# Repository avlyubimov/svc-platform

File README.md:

# SVC Platform — Smart Vehicle Controller

<p align="center">
  Open modular hardware, firmware, and mobile software for controlling
  auxiliary equipment on motorcycles and other vehicles.
</p>

**Reference Vehicle #001:** BMW R1200GS K25 2007<br>
**VIN:** WB10307A97ZU65028

## Mission

SVC should allow new functionality to be added primarily through configuration,
plugins, firmware updates, or Logic Board replacement without redesigning the
Power Board.

## Current status

Architecture v1.0 is frozen. Firmware safety, configuration, role mapping,
rule execution, CAN safety, update policy, and PWM ownership have host-tested
scaffolds.

The three boards are moving through the controlled EVT lifecycle independently:

| Board | Current repository state | Release boundary |
| --- | --- | --- |
| **PB-100** | `EVT-LAYOUT-AUTHORIZED` | Partial layout only; fabrication and production remain blocked |
| **LB-100** | `EVT-FAB-AUTHORIZED` | One segregated five-piece bare-PCB EVT package only |
| **FB-100** | `EVT-LAYOUT-AUTHORIZED` | Layout may continue; fabrication and production remain blocked |

These states describe the current `master` baseline. They do not authorize a
combined board order or production release. Detailed and machine-checked gates
are tracked in
[`docs/product/final-readiness.md`](docs/product/final-readiness.md).

## Mobile application

<p align="center">
  
  &nbsp;&nbsp;&nbsp;&nbsp;
  
</p>

SVC Mobile is being developed for iOS and Android. It provides the foundation
for live telemetry, diagnostics, vehicle data, channel control, event history,
configuration, and phone-mediated firmware updates. CHIGEE AIO-6 is treated as
a CarPlay/Android Auto projection host; the applications run on the phone.

The committed mobile baseline includes SwiftUI and Jetpack Compose
applications, BLE and protocol layers, mock data, projection scaffolds, a
GitHub Releases client, and signed-update validation. Physical channel control,
live BLE integration, and firmware transfer/installation remain disabled or
mock-backed until hardware validation closes the applicable safety gates.

The images above use only the project-owned SVC identity.
Vehicle-manufacturer artwork is not part of this repository presentation.

### SVC Ride Dashboard

Dashboard v1 is implemented for the SwiftUI and Jetpack Compose phone targets.
It uses separate versioned vehicle-performance profiles, explicit telemetry
quality states, profile-driven tachometer zones, SVC-estimated lean, Day/Night
themes, Reduce Motion, and adaptive landscape/portrait layouts. Missing CAN
signals remain `—`; gear is not inferred from speed and RPM. CarPlay and
Android Auto retain a separate, reduced information-only template.

- [Mobile overview and local build commands](software/mobile/README.md)
- [iOS application](software/mobile/ios/SVCMobile/README.md)
- [Android application](software/mobile/android/README.md)
- [Firmware update trust boundary](docs/architecture/firmware-update.md)
- [SVC identity assets](software/mobile/branding/svc/README.md)
- [Ride Dashboard implementation boundary](software/mobile/docs/ride-dashboard-roadmap.md)

## Validation

```bash
make check
```

This runs repository readiness checks, KiCad validation, firmware configuration
validation and host tests, mobile protocol tests, and release-policy checks.
The same command runs in GitHub Actions on push and pull request.

Platform-specific mobile workflows additionally build and test the Android and
iOS projects in GitHub Actions.

## Repository structure

```text
docs/                 Architecture, ADR, requirements, production docs
hardware/             KiCad and mechanical files
firmware/             Embedded firmware, bootloader, plugins
software/             SVC Studio and SVC Mobile
can-db/               Vehicle CAN databases
production/           BOM, Gerber, Pick&Place, assembly docs
tools/                Readiness, protocol, security, and release validation
```

## Board naming

- **PB-100** — Power Board, intended to remain stable for 10–15 years.
- **LB-100** — Logic Board, replaceable and upgradeable.
- **FB-100** — Front Panel Board, service interface and indicators.

## Hard rule

**Power Board is sacred.**

New features should not require Power Board redesign unless all configuration,
plugin, firmware, and Logic Board options are exhausted.

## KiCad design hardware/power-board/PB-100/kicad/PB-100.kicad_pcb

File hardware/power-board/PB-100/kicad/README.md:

# PB-100 KiCad Project

Status: `EVT-LAYOUT-AUTHORIZED`; connectivity-complete layout; fabrication blocked

This directory contains the controlled Rev.1 EVT KiCad project for PB-100.

## Current boundary

- `PB-100.kicad_pro`: project metadata scaffold.
- `PB-100.kicad_sch`: value-bearing top-level schematic with linked child
  sheets.
- `sheets/*.kicad_sch`: child sheets with role-agnostic `OUT1`..`OUT10` nets
  and the reviewed CAN1 DNP/open safety path.
- `sym-lib-table`: project-local symbol library table.
- `fp-lib-table`: project-local footprint library table.
- `lib/PB100.kicad_sym` and `lib/PB100Gen.kicad_sym`: controlled project-local
  symbols.
- `lib/PB100.pretty/`: controlled project-local footprints.
- `PB-100-routing.csv`: complete deterministic routing manifest.

The controlled `PB-100.kicad_pcb` places all 414 footprint-bound schematic
parts plus eight mechanical holes on the reviewed 150 mm x 90 mm, eight-layer
outline. It contains 5,677 segments, 910 conventional through vias, 39
adjacent-layer microvias and 38 zones. KiCad 10.0.4 refill reports zero
unconnected items; schematic parity contains only the eight intentional
board-only mounting holes.

The 39 `0.30/0.10 mm` microvias are explicit HDI manufacturing constraints.
They include stacked F.Cu-to-In3.Cu and B.Cu-to-In5.Cu transitions. U3 pads 2
and 9 also contain filled/capped conventional through via-in-pad features.
Supplier sequential-lamination, aspect-ratio, registration, filling/capping,
inspection, yield and quote acceptance remain mandatory.

ADR-0019 and ADR-0020 permit controlled board import, placement, routing,
copper pours and extraction while the final EVT schematic review remains open.
There are no manufacturing outputs; Gerber, drill, pick-and-place, BOM/CPL and
zipped manufacturing outputs remain blocked until
`EVT-FAB-AUTHORIZED` after DRC, parity, 40 A electrothermal/clamp-loop review,
DFM, connector fit and laboratory safety review.

## Source documents

- `../PB-100-schematic-capture-plan.md`
- `../PB-100-schematic-capture-work-queue.csv`
- `../PB-100-review-release-manifest.csv`
- `../PB-100-schematic-readiness-dashboard.csv`
- `../PB-100-net-naming.md`
- `../PB-100-schematic-instance-plan.csv`
- `../PB-100-schematic-instance-symbol-map.csv`
- `../PB-100-schematic-sheet-reference-map.csv`
- `../PB-100-schematic-net-domain-plan.csv`
- `../PB-100-output-channel-pin-contract.csv`
- `../PB-100-output-controller-pin-template.csv`
- `../PB-100-output-net-expansion.csv`
- `../PB-100-output-stage-design-values.csv`
- `../PB-100-input-controller-pin-template.csv`
- `../PB-100-input-protection-pin-contract.csv`
- `../PB-100-input-power-design-values.csv`
- `../PB-100-current-monitor-pin-template.csv`
- `../PB-100-logic-buck-pin-template.csv`
- `../PB-100-logic-power-design-placeholders.csv`
- `../PB-100-logic-power-design-values.csv`
- `../PB-100-kicad-prep.md`
- `../PB-100-kicad-sheet-manifest.csv`
- `../PB-100-kicad-footprint-plan.csv`
- `../PB-100-footprint-binding-inventory.csv`
- `../PB-100-symbol-mpn-readiness.csv`
- `../PB-100-symbol-capture-worklist.csv`
- `../PB-100-symbol-pin-evidence.csv`
- `../PB-100-symbol-open-items.md`
- `../PB-100-schematic-freeze-checklist.md`
- `../PB-100-pcb-layout-start-checklist.csv`
- `../PB-100-mechanical-envelope-inventory.csv`
- `../PB-100-schematic-freeze-gap-register.csv`
- `../PB-100-validation-traceability.csv`
- `../PB-100-test-point-plan.csv`
- `../PB-100-fault-response-matrix.csv`
- `../PB-100-can1-safety-verification.csv`
- `../../../../production/bom/pb100_assembly_sourcing_recheck.csv`
- `../../../../production/bom/pb100_sourcing_evidence_snapshot.csv`
- `../../../../production/board-order/three_board_footprint_binding_status.csv`
- `../../../../production/board-order/three_board_mechanical_envelope_status.csv`
- `../../../../firmware/configs/hardware/pb-100-capabilities.json`

## Next controlled work

1. Review `../PB-100-evt-fab-review-checklist.csv`, ADR-0020 and
   `../PB-100-layout-progress.md`.
2. Open `PB-100.kicad_pro` in KiCad.
3. Perform the 40 A electrothermal, switch/clamp-loop, Kelvin, rail, CAN1,
   connector and safety review against the tracked layout.
4. Obtain supplier HDI stack/DFM acceptance and filled/capped via-in-pad
   confirmation before any fabrication authorization.
5. Preserve all generic outputs, option footprints and DNP variants during
   review changes.
6. Do not create Gerbers, drills, pick-place, BOM/CPL, manufacturing ZIP files,
   fabrication packages or PCBA orders until `EVT-FAB-AUTHORIZED`.

## Validation

Run from repository root:

```bash
python3 tools/validate_pb100.py
python3 tools/validate_pb100_layout.py
```

The validator intentionally fails if manufacturing artifacts appear before
layout review and order evidence close.

The validator requires `kicad-cli` version `10.0.4`. It fails if KiCad is
missing or a different version is installed.

The validator also rejects `sheet-placeholder`/`Placeholder sheet` markers,
runs schematic ERC, requires zero reported violations, exports a temporary KiCad
S-expression netlist, checks that all child sheets in
`PB-100-kicad-sheet-manifest.csv` are linked from the top-level schematic, and
requires at least 20 schematic components plus 20 electrical nets in the exported
netlist. Empty child sheets are therefore not allowed to pass CI.

The current child sheets use passive preliminary class-symbol pins so ERC checks
hierarchy, net continuity, and capture completeness without treating abstract
planning symbols as final electrical models. Schematic freeze must replace those
abstract instances with reviewed final pin electrical types, values, footprints,
and MPN selections.

KiCad schematic and symbol files are also checked for accessory-role tokens such
as `FOG`, `USB`, `SEAT`, `CHIGEE`, `DVR`, and `BRAKE`. PB-100 output artifacts
must use generic `OUT1`..`OUT10` naming only. The protected manual-request inputs
`FOG_A_SW_IN` and `FOG_B_SW_IN` are the only explicit exceptions; they do not
assign roles to outputs and cannot bypass Output Manager authorization.

Rows in `PB-100-symbol-capture-worklist.csv` that say `preliminary symbol
created` are checked against `lib/PB100.kicad_sym`; those symbols must stay
excluded from BOM and board output until schematic freeze.

`PB-100-symbol-pin-evidence.csv` records the official data-sheet pin tables used
for concrete MPN symbols and the internal schematic-class pin contracts used for
non-final class symbols. Validation checks each recorded pin number/name against
the KiCad symbol library.

`PB100_JPB1_100PIN_PRELIM` is generated from
`PB-100-b2b-pin-map.csv`; validation checks all 100 connector pin names and
numbers directly against that map.

The readiness dashboard and pin/value contract CSVs are checked against the
instance map, JPB1 pin map, net-domain plan, and freeze policy. Layout-start
work is now controlled by `../PB-100-pcb-layout-start-checklist.csv`.

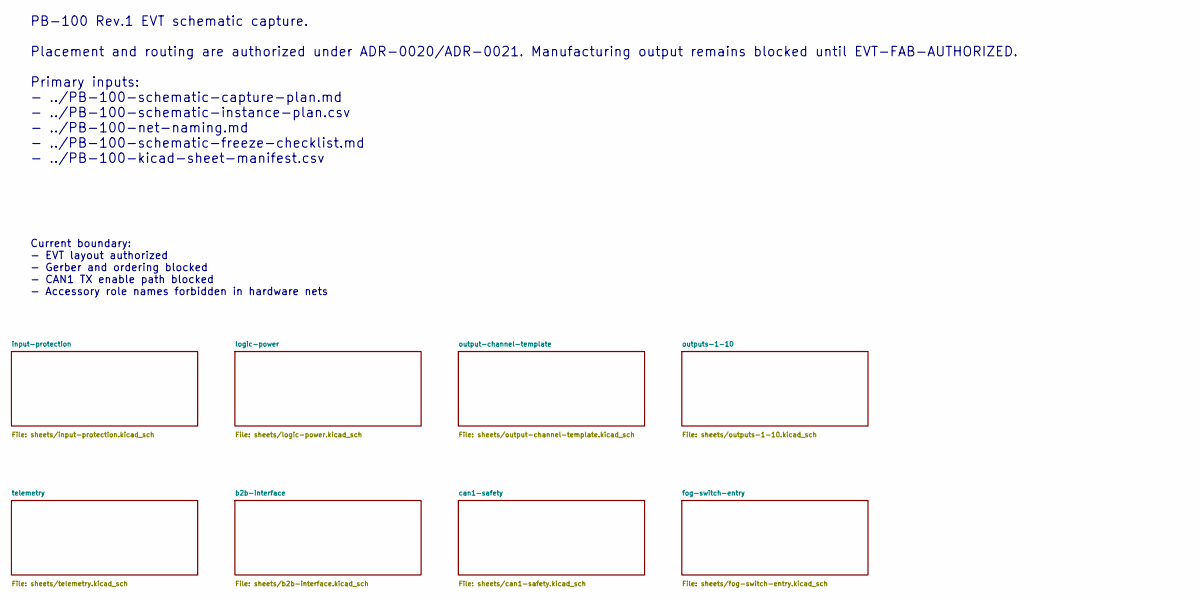
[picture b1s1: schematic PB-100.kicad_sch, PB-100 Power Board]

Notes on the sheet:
PB-100 Rev.1 EVT schematic capture. Placement and routing are authorized under ADR-0020/ADR-0021. Manufacturing output remains blocked until EVT-FAB-AUTHORIZED. Primary inputs: - ../PB-100-schematic-capture-plan.md - ../PB-100-schematic-instance-plan.csv - ../PB-100-net-naming.md - ../PB-100-schema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
Current boundary: - EVT layout authorized - Gerber and ordering blocked - CAN1 TX enable path blocked - Accessory role names forbidden in hardware nets

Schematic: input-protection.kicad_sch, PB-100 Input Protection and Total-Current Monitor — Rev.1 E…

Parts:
C20: 100nF 50V X7R DIFF; C0603
C21: 1nF 100V C0G; C0603
C22: 100nF 16V X7R; C0603
C23: 1nF PB I2C INT FILTER DNP; C0603; not fitted
C24: 10nF 50V X7R; C0603
CCAP1: 100nF 25V X7R; C0603
CSN1: 1nF 100V C0G DNP; C0603; not fitted
CSN2: 1nF 200V C0G DNP; C0603; not fitted
CVS1: CGA6N3X7R2A225M230AE 2.2uF 100V X7R; Ceff>=1uF@56V; C1210
D1: SM8S33AHM3/I; DO-218AC_Vishay_SM8S; not fitted
DZVS1: 56V AUTOMOTIVE ZENER; SOD-123F
J1: INPUT_CONNECTOR_CLASS_PRELIM (OFF-BOARD)
JIN1: 40A PCB PIGTAIL TO NEAR-BATTERY 50A FUSE; POWER_PIGTAIL_2xTH_40A
JISO1: EVT INPUT-STAGE ISOLATION LINK — FITTED FOR NORMA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; EVT_INPUT_ISOLATION_LINK_M4
Q1: IAUT300N08S5N012ATMA2; PG-HSOF-8-1_TOLL_Infineon
Q2: IAUTN15S6N025ATMA1; PG-HSOF-8-1_TOLL_Infineon
R3, R4: 42.2k 1%; R0603
R5: 1.00k 1%; R0603
R6: 10k 1%; R0603
R7: 0R REPLACEABLE Q1 GATE; R0603
R8: 0R REPLACEABLE Q2 GATE; R0603
R20, R21: 10R 0.1% SHUNT FILTER; R0603
R22: 1k 1% VBUS FILTER; R0603
R23: 10k PB I2C SDA PULL DNP; R0603; not fitted
R24: 10k PB I2C SCL PULL DNP; R0603; not fitted
R25: 47k PB I2C INT PULL DNP; R0603; not fitted
R26: 0R INPUT FAULT AGGREGATE; R0603
R27: 200k 0.1% 100V; R0603
R28: 10k 0.1%; R0603
R29: 1k 0.1%; R0603
RSH1: CSS4J-4026R-L500F 0.5mR 5W FOUR-TERMINAL; CSS4J-4026_Bourns
RSN1: 100R DNP Q1 DAMPING; R0603; not fitted
RSN2: 100R DNP Q2 DAMPING; R0603; not fitted
TP001: TEST GND; TestPoint_SMD_1.5mm
TP003: TEST VBAT_RAW; TestPoint_SMD_1.5mm
TP004: TEST VBAT_REV_PROT; TestPoint_SMD_1.5mm
TP005: TEST VBAT_PROT; TestPoint_SMD_1.5mm
TP006: TEST IIN_SHUNT_HI; TestPoint_SMD_1.5mm
TP007: TEST IIN_SHUNT_LO; TestPoint_SMD_1.5mm
TP008: TEST VBAT_SENSE; TestPoint_SMD_1.5mm
TP009: TEST IIN_SENSE; TestPoint_SMD_1.5mm
TP062: TEST Q1_GATE; TestPoint_SMD_1.5mm
TP063: TEST Q2_GATE; TestPoint_SMD_1.5mm
TP064: TEST INPUT_COMMON_SOURCE; TestPoint_SMD_1.5mm
TP065: TEST VBAT_PROT_PRELINK; TestPoint_SMD_1.5mm
U1: LM74930QRGERQ1; VQFN-24_RGE_4x4mm_P0.5mm_EP2.4mm
U2: INA228AQDGSRQ1 TOTAL CURRENT MONITOR; VSSOP-10_L3.0-W3.0-P0.50-LS4.9-BL

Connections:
IIN_MON_N: C20.2, R21.2, U2.9 (IN-)
IIN_MON_P: C20.1, R20.2, U2.10 (IN+)
IIN_SHUNT_HI: R20.1, RSH1.3 (SNS_IN), TP006.1 (IIN_SHUNT_HI)
IIN_SHUNT_LO: R21.1, RSH1.4 (SNS_OUT), TP007.1 (IIN_SHUNT_LO)
IIN_VBUS_FILTERED: C21.1, R22.2, U2.8 (VBUS)
INPUT_COMMON_SOURCE: CSN1.2, CSN2.2, Q1.2 (S), Q1.3 (S), Q1.4 (S), Q1.5 (S), Q1.6 (S), Q1.7 (S), Q1.8 (S), Q2.2 (S), Q2.3 (S), Q2.4 (S), Q2.5 (S), Q2.6 (S), Q2.7 (S), Q2.8 (S), TP064.1 (INPUT_COMMON_SOURCE), U1.2 (A), U1.15 (OUT)
INPUT_PROT_FAULT_N: R26.1, U1.12 (FLT)
LB_3V3_IO: R23.1, R24.1, R25.1; also elsewhere on the board
LM74930_CAP: CCAP1.1, U1.23 (CAP)
LM74930_OV: R4.2, R5.1, U1.5 (OV)
LM74930_OV_TOP_MID: R3.2, R4.1
LM74930_VS: CCAP1.2, CVS1.1, DZVS1.1, R6.2, U1.4 (UVLO), U1.6 (EN), U1.7 (MODE), U1.22 (VS)
PB_5V_OUT: C22.1, U2.6 (VS); also elsewhere on the board
Q1_DGATE: R7.1, U1.1 (DGATE)
Q1_GATE: Q1.1 (G), R7.2, TP062.1 (Q1_GATE)
Q1_SNUB: CSN1.1, RSN1.2
Q2_GATE: Q2.1 (G), R8.2, TP063.1 (Q2_GATE)
Q2_HGATE: R8.1, U1.14 (HGATE)
Q2_SNUB: CSN2.1, RSN2.2
VBAT_PROT: JISO1.2 (BOARD_LOADS), R22.1, R27.1, TP005.1 (VBAT_PROT); also elsewhere on the board
VBAT_PROT_PRELINK: JISO1.1 (INPUT_STAGE), RSH1.2 (PWR_OUT), TP065.1 (VBAT_PROT_PRELINK)
VBAT_RAW: D1.1 (K), J1.1 (VBAT_RAW), JIN1.1 (VBAT_RAW), Q2.Tab (D), R3.1, R6.1, RSN2.1, TP003.1 (VBAT_RAW)
VBAT_REV_PROT: Q1.Tab (D), RSH1.1 (PWR_IN), RSN1.1, TP004.1 (VBAT_REV_PROT), U1.18 (ISCP), U1.19 (CS-), U1.20 (CS+), U1.24 (C)
VBAT_SENSE_RAW: R27.2, R28.1, R29.1

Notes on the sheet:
Work queue: CAP-INP. ADR-0018/0019/0020 implementation. The raw-side 150 V Q2 and protected-side 80 V Q1 retain the reviewed LM74930-Q1 common-source hard-cutoff topology. RSH1 is a 0.5 mOhm four-terminal shunt. JISO1 is the mandatory removable input-stage isolation link; opening it prevents VBAT_P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

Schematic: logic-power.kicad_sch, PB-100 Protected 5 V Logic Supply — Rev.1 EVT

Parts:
C30: 2.2uF 100V X7R; C1210
C31: 100nF 100V X7R; C0805
C32: 10uF 100V BULK CANDIDATE; C1210
C33: 2.2nF 50V X7R; C0603
C34, C35: 22uF 10V X7R; C1210
C36: 100nF 16V X7R; C0603
C37: 10nF PGOOD FILTER DNP; C0603; not fitted
C38: 3.3nF 100V C0G TYPE3 CA; C0603
C39: 180pF 50V C0G TYPE3 CB; C0603
C40: 1nF 100V C0G DNP; C0603; not fitted
L1: 47uH SHIELDED AEC-Q200; Isat>=2.2A Irms>=1.2A; Inductor_12x12mm
R30: 332k 1%; R0603
R31: 100k 1%; R0603
R32: 41.2k 1%; R0603
R33: 158k 0.1%; R0603
R34: 49.9k 0.1%; R0603
R35: 47k PGOOD PULL-UP; R0603
R36: 110k 1% TYPE3 RA; R0603
R37: 100R BUCK SNUBBER DNP; R0603; not fitted
TP010: TEST PB_5V_OUT; TestPoint_SMD_1.5mm
TP011: TEST PB_PWR_GOOD; TestPoint_SMD_1.5mm
U3: LM5164QDDATQ1 100V 1A BUCK; SOIC-8_L4.9-W3.9-P1.27-LS6.0-BL-EP2.9

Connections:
BUCK_BST: C33.1, U3.7 (BST)
BUCK_EN_UVLO: R30.2, R31.1, U3.3 (EN/UVLO)
BUCK_FB: C39.2, R33.2, R34.1, U3.5 (FB)
BUCK_RAMP: C38.2, C39.1, R36.1
BUCK_RON_SET: R32.1, U3.4 (RON)
BUCK_SNUB: C40.1, R37.2
BUCK_SW: C33.2, C38.1, L1.1, R37.1, U3.8 (SW)
LB_3V3_IO: R35.1; also elsewhere on the board
PB_5V_OUT: C34.1, C35.1, C36.1, L1.2, R33.1, R36.2, TP010.1 (PB_5V_OUT); also elsewhere on the board
VBAT_PROT: C30.1, C31.1, C32.1, R30.1, U3.2 (VIN); also elsewhere on the board

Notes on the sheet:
Work queue: CAP-LOGIC. LM5164-Q1 100 V synchronous buck, 5.0 V / 1 A planning limit. The 300 kHz candidate uses 41.2k RON, 47uH shielded inductor, and a type-3 ripple-injection network. Switch-node copper must remain compact; thermal vias under the exposed pad and routed EMI evidence are required a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

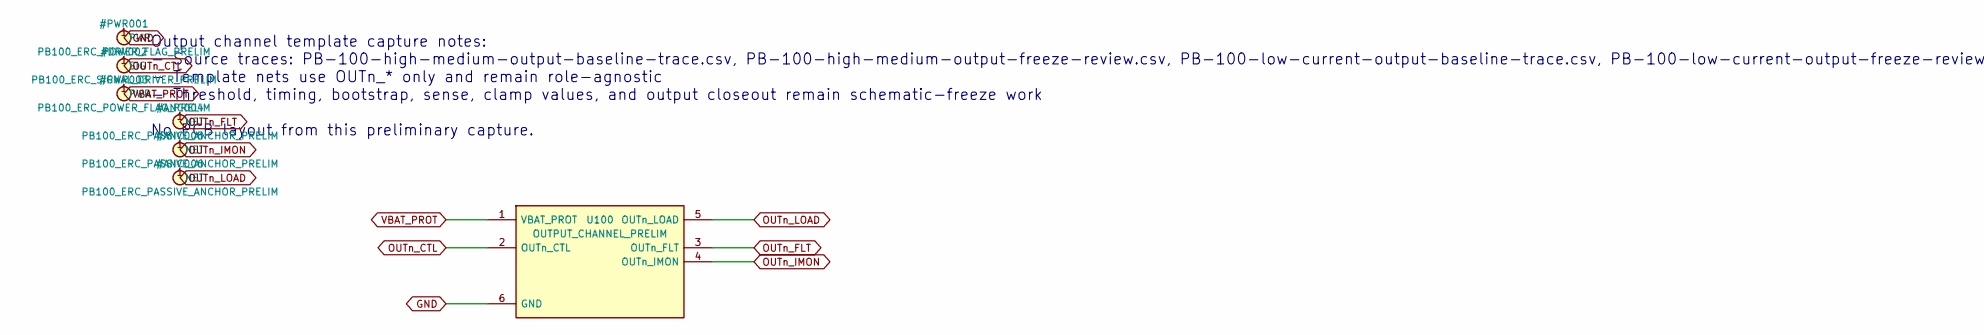
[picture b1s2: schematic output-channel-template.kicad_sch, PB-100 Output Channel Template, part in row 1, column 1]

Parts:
U100: OUTPUT_CHANNEL_PRELIM

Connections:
unnamed: U100.1 (VBAT_PROT), U100.6 (GND)
unnamed: U100.3 (OUTn_FLT), U100.4 (OUTn_IMON), U100.5 (OUTn_LOAD)

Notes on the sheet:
Output channel template capture notes: - Source traces: PB-100-high-medium-output-baseline-trace.csv, PB-100-high-medium-output-freeze-review.csv, PB-100-low-current-output-baseline-trace.csv, PB-100-low-current-output-freeze-review.csv, PB-100-output-stage-value-freeze-checklist.csv, PB-100-output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

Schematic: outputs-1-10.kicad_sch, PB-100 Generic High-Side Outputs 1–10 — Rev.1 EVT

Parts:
C1101, C1201, C1301, C1401, C1501, C1601, C1701, C1801, C1901, C2001: 680nF 16V X7R TMR; C0603
C1102, C1202, C1302, C1402, C1502, C1602, C1702, C1802, C1902, C2002: 470nF 25V X7R BST; C0603
C1103, C1203, C1303, C1403, C1503, C1603, C1703, C1803, C1903, C2003: 1nF 50V C0G ISCP; C0603
C1104, C1204, C1304, C1404, C1504, C1604, C1704, C1804, C1904, C2004: 100nF 100V X7R VS; C0805
C1105, C1205, C1305, C1405, C1505, C1605, C1705, C1805, C1905, C2005: 10nF 50V X7R IMON; C0603
C1106, C1206, C1306, C1406, C1506, C1606, C1706, C1806, C1906, C2006: 1nF 25V DNP GATE-SLEW; C0603; not fitted
C1107, C1207, C1307, C1407, C1507, C1607, C1707, C1807, C1907, C2007: 1nF 100V C0G DNP SNUBBER; C0603; not fitted
DCL101, DCL102, DCL103, DCL104, DCL105, DCL106, DCL107, DCL108, DCL109, DCL110: STPS40170CGY-TR 2x20A 170V COMMON-CATHODE; D2PAK_3_CommonCathode
F101, F102, F103, F104, F105, F106, F107, F108, F109, F110: OUTPUT_FUSE_CLASS_PRELIM (OFF-BOARD)
J101, J102, J103, J104, J105, J106, J107, J108, J109, J110: OUTPUT_CONNECTOR_CLASS_PRELIM (OFF-BOARD)
Q101, Q102, Q103, Q104, Q105, Q106, Q107, Q108, Q109, Q110: IAUT300N08S5N012ATMA2; PG-HSOF-8-1_TOLL_Infineon
QT101, QT102, QT103, QT104, QT105, QT106, QT107, QT108, QT109, QT110: MMBT3904-Q REMOTE TEMP DIODE; SOT-23-3_DBZ_TI
R1101, R1201, R1301, R1401, R1501, R1601, R1701, R1801, R1901, R2001: 470k 1%; R0603
R1102, R1202, R1302, R1402, R1502, R1602, R1702, R1802, R1902, R2002: 103k 1%; R0603
R1103, R1203, R1303, R1403, R1503, R1603, R1703, R1803, R1903, R2003: 12.4k 1%; R0603
R1104, R1204, R1304, R1404, R1504, R1604, R1704, R1804, R1904, R2004: 100R 1% RSET; R0603
R1105, R1305, R1405, R1505, R1605, R1705, R1805, R1905, R2005: 49.9k 1% RIWRN; R0603
R1106: 3.40k 1% RISCP; R0603
R1107, R1207, R1307, R1407, R1507, R1607, R1707, R1807, R1907, R2007: 12.1k 1% RIMON; R0603
R1108, R1208, R1308, R1408, R1508, R1608, R1708, R1808, R1908, R2008: 1k 1% IMON ADC SERIES; R0603
R1109, R1209, R1309, R1409, R1509, R1609, R1709, R1809, R1909, R2009: 100k CTL DEFAULT-OFF; R0603
R1110, R1210, R1310, R1410, R1510, R1610, R1710, R1810, R1910, R2010: 3.3R 1% REPLACEABLE PU; R0603
R1111, R1211, R1311, R1411, R1511, R1611, R1711, R1811, R1911, R2011: 0R REPLACEABLE PD; R0603
R1112, R1212, R1312, R1412, R1512, R1612, R1712, R1812, R1912, R2012: 10k FLT PULL-UP; R0603
R1113, R1213, R1313, R1413, R1513, R1613, R1713, R1813, R1913, R2013: 100R DNP DRAIN-SOURCE SNUBBER; R0603; not fitted
R1205: 67.3k 1% RIWRN; R0603
R1206: 2.61k 1% RISCP; R0603
R1306, R1406, R1606, R1706, R2006: 3.83k 1% RISCP; R0603
R1506, R1806, R1906: 3.74k 1% RISCP; R0603
RSH101: CSS4J-4026 1.0mR FOUR-TERMINAL; CSS4J-4026_Bourns
RSH102: CSS4J-4026 0.5mR FOUR-TERMINAL; CSS4J-4026_Bourns
RSH103, RSH104, RSH106, RSH107, RSH110: CSS4J-4026 1.5mR FOUR-TERMINAL; CSS4J-4026_Bourns
RSH105, RSH108, RSH109: CSS4J-4026 3.0mR FOUR-TERMINAL; CSS4J-4026_Bourns
TP022: TEST OUT1_CTL; TestPoint_SMD_1.5mm
TP023: TEST OUT1_FLT; TestPoint_SMD_1.5mm
TP024: TEST OUT1_IMON; TestPoint_SMD_1.5mm
TP025: TEST OUT1_SWITCHED; TestPoint_SMD_1.5mm
TP026: TEST OUT2_CTL; TestPoint_SMD_1.5mm
TP027: TEST OUT2_FLT; TestPoint_SMD_1.5mm
TP028: TEST OUT2_IMON; TestPoint_SMD_1.5mm
TP029: TEST OUT2_SWITCHED; TestPoint_SMD_1.5mm
TP030: TEST OUT3_CTL; TestPoint_SMD_1.5mm
TP031: TEST OUT3_FLT; TestPoint_SMD_1.5mm
TP032: TEST OUT3_IMON; TestPoint_SMD_1.5mm
TP033: TEST OUT3_SWITCHED; TestPoint_SMD_1.5mm
TP034: TEST OUT4_CTL; TestPoint_SMD_1.5mm
TP035: TEST OUT4_FLT; TestPoint_SMD_1.5mm
TP036: TEST OUT4_IMON; TestPoint_SMD_1.5mm
TP037: TEST OUT4_SWITCHED; TestPoint_SMD_1.5mm
TP038: TEST OUT5_CTL; TestPoint_SMD_1.5mm
TP039: TEST OUT5_FLT; TestPoint_SMD_1.5mm
TP040: TEST OUT5_IMON; TestPoint_SMD_1.5mm
TP041: TEST OUT5_SWITCHED; TestPoint_SMD_1.5mm
TP042: TEST OUT6_CTL; TestPoint_SMD_1.5mm
TP043: TEST OUT6_FLT; TestPoint_SMD_1.5mm
TP044: TEST OUT6_IMON; TestPoint_SMD_1.5mm
TP045: TEST OUT6_SWITCHED; TestPoint_SMD_1.5mm
TP046: TEST OUT7_CTL; TestPoint_SMD_1.5mm
TP047: TEST OUT7_FLT; TestPoint_SMD_1.5mm
TP048: TEST OUT7_IMON; TestPoint_SMD_1.5mm
TP049: TEST OUT7_SWITCHED; TestPoint_SMD_1.5mm
TP050: TEST OUT8_CTL; TestPoint_SMD_1.5mm
TP051: TEST OUT8_FLT; TestPoint_SMD_1.5mm
TP052: TEST OUT8_IMON; TestPoint_SMD_1.5mm
TP053: TEST OUT8_SWITCHED; TestPoint_SMD_1.5mm
TP054: TEST OUT9_CTL; TestPoint_SMD_1.5mm
TP055: TEST OUT9_FLT; TestPoint_SMD_1.5mm
TP056: TEST OUT9_IMON; TestPoint_SMD_1.5mm
TP057: TEST OUT9_SWITCHED; TestPoint_SMD_1.5mm
TP058: TEST OUT10_CTL; TestPoint_SMD_1.5mm
TP059: TEST OUT10_FLT; TestPoint_SMD_1.5mm
TP060: TEST OUT10_IMON; TestPoint_SMD_1.5mm
TP061: TEST OUT10_SWITCHED; TestPoint_SMD_1.5mm
U101, U102, U103, U104, U105, U106, U107, U108, U109, U110: TPS48110AQDGXRQ1; VSSOP-20_19P-L5.0-W3.0-P0.50-LS5.0-BL_PE16
W101: OUT1 PCB PIGTAIL TO OFF-BOARD FUSE/SEALED CONNECT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; POWER_PIGTAIL_2xTH_20A
W102: OUT2 PCB PIGTAIL TO OFF-BOARD FUSE/SEALED CONNECT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; POWER_PIGTAIL_2xTH_20A
W103: OUT3 PCB PIGTAIL TO OFF-BOARD FUSE/SEALED CONNECT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; POWER_PIGTAIL_2xTH_20A
W104: OUT4 PCB PIGTAIL TO OFF-BOARD FUSE/SEALED CONNECT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; POWER_PIGTAIL_2xTH_20A
W105: OUT5 PCB PIGTAIL TO OFF-BOARD FUSE/SEALED CONNECT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; POWER_PIGTAIL_2xTH_20A
W106: OUT6 PCB PIGTAIL TO OFF-BOARD FUSE/SEALED CONNECT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; POWER_PIGTAIL_2xTH_20A
W107: OUT7 PCB PIGTAIL TO OFF-BOARD FUSE/SEALED CONNECT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; POWER_PIGTAIL_2xTH_20A
W108: OUT8 PCB PIGTAIL TO OFF-BOARD FUSE/SEALED CONNECT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; POWER_PIGTAIL_2xTH_20A
W109: OUT9 PCB PIGTAIL TO OFF-BOARD FUSE/SEALED CONNECT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; POWER_PIGTAIL_2xTH_20A
W110: OUT10 PCB PIGTAIL TO OFF-BOARD FUSE/SEALED CONNEC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; POWER_PIGTAIL_2xTH_20A

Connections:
LB_3V3_IO: R1112.1, R1212.1, R1312.1, R1412.1, R1512.1, R1612.1, R1712.1, R1812.1, R1912.1, R2012.1; also elsewhere on the board
unnamed: F101.2 (OUT), J101.1 (POS)
unnamed: F102.2 (OUT), J102.1 (POS)
unnamed: F103.2 (OUT), J103.1 (POS)
unnamed: F104.2 (OUT), J104.1 (POS)
unnamed: F105.2 (OUT), J105.1 (POS)
unnamed: F106.2 (OUT), J106.1 (POS)
unnamed: F107.2 (OUT), J107.1 (POS)
unnamed: F108.2 (OUT), J108.1 (POS)
unnamed: F109.2 (OUT), J109.1 (POS)
unnamed: F110.2 (OUT), J110.1 (POS)
OUT1_BST: C1102.1, U101.12 (BST)
OUT1_CS_N: C1103.2, RSH101.4 (SNS_OUT), U101.17 (CS-)
OUT1_CS_P: R1104.2, U101.18 (CS+)
OUT1_CS_P_KELVIN: R1104.1, R1106.1, RSH101.3 (SNS_IN)
OUT1_DIODE: QT101.2 (B), QT101.3 (C), U101.10 (DIODE)
OUT1_EN_UVLO: R1102.2, R1103.1, U101.1 (EN/UVLO)
OUT1_FET_DRAIN: Q101.Tab (D), R1113.1, RSH101.2 (PWR_OUT)
OUT1_GATE: C1106.1, Q101.1 (G), R1110.2, R1111.2
OUT1_IMON_RAW: R1107.1, R1108.1, U101.7 (IMON)
OUT1_ISCP: C1103.1, R1106.2, U101.19 (ISCP)
OUT1_IWRN: R1105.1, U101.8 (IWRN)
OUT1_OV: R1101.2, R1102.1, U101.2 (OV)
OUT1_PD: R1111.1, U101.14 (PD)
OUT1_PU: R1110.1, U101.15 (PU)
OUT1_SNUB: C1107.1, R1113.2
OUT1_SWITCHED: C1102.2, C1106.2, C1107.2, DCL101.2 (K), F101.1 (IN), Q101.2 (S), Q101.3 (S), Q101.4 (S), Q101.5 (S), Q101.6 (S), Q101.7 (S), Q101.8 (S), TP025.1 (OUT1_SWITCHED), U101.13 (SRC), W101.1 (POS)
OUT1_TMR: C1101.1, U101.9 (TMR)
OUT2_BST: C1202.1, U102.12 (BST)
OUT2_CS_N: C1203.2, RSH102.4 (SNS_OUT), U102.17 (CS-)
OUT2_CS_P: R1204.2, U102.18 (CS+)
OUT2_CS_P_KELVIN: R1204.1, R1206.1, RSH102.3 (SNS_IN)
OUT2_DIODE: QT102.2 (B), QT102.3 (C), U102.10 (DIODE)
OUT2_EN_UVLO: R1202.2, R1203.1, U102.1 (EN/UVLO)
OUT2_FET_DRAIN: Q102.Tab (D), R1213.1, RSH102.2 (PWR_OUT)
OUT2_GATE: C1206.1, Q102.1 (G), R1210.2, R1211.2
OUT2_IMON_RAW: R1207.1, R1208.1, U102.7 (IMON)
OUT2_ISCP: C1203.1, R1206.2, U102.19 (ISCP)
OUT2_IWRN: R1205.1, U102.8 (IWRN)
OUT2_OV: R1201.2, R1202.1, U102.2 (OV)
OUT2_PD: R1211.1, U102.14 (PD)
OUT2_PU: R1210.1, U102.15 (PU)
OUT2_SNUB: C1207.1, R1213.2
OUT2_SWITCHED: C1202.2, C1206.2, C1207.2, DCL102.2 (K), F102.1 (IN), Q102.2 (S), Q102.3 (S), Q102.4 (S), Q102.5 (S), Q102.6 (S), Q102.7 (S), Q102.8 (S), TP029.1 (OUT2_SWITCHED), U102.13 (SRC), W102.1 (POS)
OUT2_TMR: C1201.1, U102.9 (TMR)
OUT3_BST: C1302.1, U103.12 (BST)
OUT3_CS_N: C1303.2, RSH103.4 (SNS_OUT), U103.17 (CS-)
OUT3_CS_P: R1304.2, U103.18 (CS+)
OUT3_CS_P_KELVIN: R1304.1, R1306.1, RSH103.3 (SNS_IN)
OUT3_DIODE: QT103.2 (B), QT103.3 (C), U103.10 (DIODE)
OUT3_EN_UVLO: R1302.2, R1303.1, U103.1 (EN/UVLO)
OUT3_FET_DRAIN: Q103.Tab (D), R1313.1, RSH103.2 (PWR_OUT)
OUT3_GATE: C1306.1, Q103.1 (G), R1310.2, R1311.2
OUT3_IMON_RAW: R1307.1, R1308.1, U103.7 (IMON)
OUT3_ISCP: C1303.1, R1306.2, U103.19 (ISCP)
OUT3_IWRN: R1305.1, U103.8 (IWRN)
OUT3_OV: R1301.2, R1302.1, U103.2 (OV)
OUT3_PD: R1311.1, U103.14 (PD)
OUT3_PU: R1310.1, U103.15 (PU)
OUT3_SNUB: C1307.1, R1313.2
OUT3_SWITCHED: C1302.2, C1306.2, C1307.2, DCL103.2 (K), F103.1 (IN), Q103.2 (S), Q103.3 (S), Q103.4 (S), Q103.5 (S), Q103.6 (S), Q103.7 (S), Q103.8 (S), TP033.1 (OUT3_SWITCHED), U103.13 (SRC), W103.1 (POS)
OUT3_TMR: C1301.1, U103.9 (TMR)
OUT4_BST: C1402.1, U104.12 (BST)
OUT4_CS_N: C1403.2, RSH104.4 (SNS_OUT), U104.17 (CS-)
OUT4_CS_P: R1404.2, U104.18 (CS+)
OUT4_CS_P_KELVIN: R1404.1, R1406.1, RSH104.3 (SNS_IN)
OUT4_DIODE: QT104.2 (B), QT104.3 (C), U104.10 (DIODE)
OUT4_EN_UVLO: R1402.2, R1403.1, U104.1 (EN/UVLO)
OUT4_FET_DRAIN: Q104.Tab (D), R1413.1, RSH104.2 (PWR_OUT)
OUT4_GATE: C1406.1, Q104.1 (G), R1410.2, R1411.2
OUT4_IMON_RAW: R1407.1, R1408.1, U104.7 (IMON)
OUT4_ISCP: C1403.1, R1406.2, U104.19 (ISCP)
OUT4_IWRN: R1405.1, U104.8 (IWRN)
OUT4_OV: R1401.2, R1402.1, U104.2 (OV)
OUT4_PD: R1411.1, U104.14 (PD)
OUT4_PU: R1410.1, U104.15 (PU)
OUT4_SNUB: C1407.1, R1413.2
OUT4_SWITCHED: C1402.2, C1406.2, C1407.2, DCL104.2 (K), F104.1 (IN), Q104.2 (S), Q104.3 (S), Q104.4 (S), Q104.5 (S), Q104.6 (S), Q104.7 (S), Q104.8 (S), TP037.1 (OUT4_SWITCHED), U104.13 (SRC), W104.1 (POS)
OUT4_TMR: C1401.1, U104.9 (TMR)
OUT5_BST: C1502.1, U105.12 (BST)
OUT5_CS_N: C1503.2, RSH105.4 (SNS_OUT), U105.17 (CS-)
OUT5_CS_P: R1504.2, U105.18 (CS+)
OUT5_CS_P_KELVIN: R1504.1, R1506.1, RSH105.3 (SNS_IN)
OUT5_DIODE: QT105.2 (B), QT105.3 (C), U105.10 (DIODE)
OUT5_EN_UVLO: R1502.2, R1503.1, U105.1 (EN/UVLO)
OUT5_FET_DRAIN: Q105.Tab (D), R1513.1, RSH105.2 (PWR_OUT)
OUT5_GATE: C1506.1, Q105.1 (G), R1510.2, R1511.2
OUT5_IMON_RAW: R1507.1, R1508.1, U105.7 (IMON)
OUT5_ISCP: C1503.1, R1506.2, U105.19 (ISCP)
OUT5_IWRN: R1505.1, U105.8 (IWRN)
OUT5_OV: R1501.2, R1502.1, U105.2 (OV)
OUT5_PD: R1511.1, U105.14 (PD)
OUT5_PU: R1510.1, U105.15 (PU)
OUT5_SNUB: C1507.1, R1513.2
OUT5_SWITCHED: C1502.2, C1506.2, C1507.2, DCL105.2 (K), F105.1 (IN), Q105.2 (S), Q105.3 (S), Q105.4 (S), Q105.5 (S), Q105.6 (S), Q105.7 (S), Q105.8 (S), TP041.1 (OUT5_SWITCHED), U105.13 (SRC), W105.1 (POS)
OUT5_TMR: C1501.1, U105.9 (TMR)
OUT6_BST: C1602.1, U106.12 (BST)
OUT6_CS_N: C1603.2, RSH106.4 (SNS_OUT), U106.17 (CS-)
OUT6_CS_P: R1604.2, U106.18 (CS+)
OUT6_CS_P_KELVIN: R1604.1, R1606.1, RSH106.3 (SNS_IN)
OUT6_DIODE: QT106.2 (B), QT106.3 (C), U106.10 (DIODE)
OUT6_EN_UVLO: R1602.2, R1603.1, U106.1 (EN/UVLO)
OUT6_FET_DRAIN: Q106.Tab (D), R1613.1, RSH106.2 (PWR_OUT)
OUT6_GATE: C1606.1, Q106.1 (G), R1610.2, R1611.2
OUT6_IMON_RAW: R1607.1, R1608.1, U106.7 (IMON)
OUT6_ISCP: C1603.1, R1606.2, U106.19 (ISCP)
OUT6_IWRN: R1605.1, U106.8 (IWRN)
OUT6_OV: R1601.2, R1602.1, U106.2 (OV)
OUT6_PD: R1611.1, U106.14 (PD)
OUT6_PU: R1610.1, U106.15 (PU)
OUT6_SNUB: C1607.1, R1613.2
OUT6_SWITCHED: C1602.2, C1606.2, C1607.2, DCL106.2 (K), F106.1 (IN), Q106.2 (S), Q106.3 (S), Q106.4 (S), Q106.5 (S), Q106.6 (S), Q106.7 (S), Q106.8 (S), TP045.1 (OUT6_SWITCHED), U106.13 (SRC), W106.1 (POS)
OUT6_TMR: C1601.1, U106.9 (TMR)
OUT7_BST: C1702.1, U107.12 (BST)
OUT7_CS_N: C1703.2, RSH107.4 (SNS_OUT), U107.17 (CS-)
OUT7_CS_P: R1704.2, U107.18 (CS+)
OUT7_CS_P_KELVIN: R1704.1, R1706.1, RSH107.3 (SNS_IN)
OUT7_DIODE: QT107.2 (B), QT107.3 (C), U107.10 (DIODE)
OUT7_EN_UVLO: R1702.2, R1703.1, U107.1 (EN/UVLO)
OUT7_FET_DRAIN: Q107.Tab (D), R1713.1, RSH107.2 (PWR_OUT)
OUT7_GATE: C1706.1, Q107.1 (G), R1710.2, R1711.2
OUT7_IMON_RAW: R1707.1, R1708.1, U107.7 (IMON)
OUT7_ISCP: C1703.1, R1706.2, U107.19 (ISCP)
OUT7_IWRN: R1705.1, U107.8 (IWRN)
OUT7_OV: R1701.2, R1702.1, U107.2 (OV)
OUT7_PD: R1711.1, U107.14 (PD)
OUT7_PU: R1710.1, U107.15 (PU)
OUT7_SNUB: C1707.1, R1713.2
OUT7_SWITCHED: C1702.2, C1706.2, C1707.2, DCL107.2 (K), F107.1 (IN), Q107.2 (S), Q107.3 (S), Q107.4 (S), Q107.5 (S), Q107.6 (S), Q107.7 (S), Q107.8 (S), TP049.1 (OUT7_SWITCHED), U107.13 (SRC), W107.1 (POS)
OUT7_TMR: C1701.1, U107.9 (TMR)
OUT8_BST: C1802.1, U108.12 (BST)
OUT8_CS_N: C1803.2, RSH108.4 (SNS_OUT), U108.17 (CS-)
OUT8_CS_P: R1804.2, U108.18 (CS+)
OUT8_CS_P_KELVIN: R1804.1, R1806.1, RSH108.3 (SNS_IN)
OUT8_DIODE: QT108.2 (B), QT108.3 (C), U108.10 (DIODE)
OUT8_EN_UVLO: R1802.2, R1803.1, U108.1 (EN/UVLO)
OUT8_FET_DRAIN: Q108.Tab (D), R1813.1, RSH108.2 (PWR_OUT)
OUT8_GATE: C1806.1, Q108.1 (G), R1810.2, R1811.2
OUT8_IMON_RAW: R1807.1, R1808.1, U108.7 (IMON)
OUT8_ISCP: C1803.1, R1806.2, U108.19 (ISCP)
OUT8_IWRN: R1805.1, U108.8 (IWRN)
OUT8_OV: R1801.2, R1802.1, U108.2 (OV)
OUT8_PD: R1811.1, U108.14 (PD)
OUT8_PU: R1810.1, U108.15 (PU)
OUT8_SNUB: C1807.1, R1813.2
OUT8_SWITCHED: C1802.2, C1806.2, C1807.2, DCL108.2 (K), F108.1 (IN), Q108.2 (S), Q108.3 (S), Q108.4 (S), Q108.5 (S), Q108.6 (S), Q108.7 (S), Q108.8 (S), TP053.1 (OUT8_SWITCHED), U108.13 (SRC), W108.1 (POS)
OUT8_TMR: C1801.1, U108.9 (TMR)
OUT9_BST: C1902.1, U109.12 (BST)
OUT9_CS_N: C1903.2, RSH109.4 (SNS_OUT), U109.17 (CS-)
OUT9_CS_P: R1904.2, U109.18 (CS+)
OUT9_CS_P_KELVIN: R1904.1, R1906.1, RSH109.3 (SNS_IN)
OUT9_DIODE: QT109.2 (B), QT109.3 (C), U109.10 (DIODE)
OUT9_EN_UVLO: R1902.2, R1903.1, U109.1 (EN/UVLO)
OUT9_FET_DRAIN: Q109.Tab (D), R1913.1, RSH109.2 (PWR_OUT)
OUT9_GATE: C1906.1, Q109.1 (G), R1910.2, R1911.2
OUT9_IMON_RAW: R1907.1, R1908.1, U109.7 (IMON)
OUT9_ISCP: C1903.1, R1906.2, U109.19 (ISCP)
OUT9_IWRN: R1905.1, U109.8 (IWRN)
OUT9_OV: R1901.2, R1902.1, U109.2 (OV)
OUT9_PD: R1911.1, U109.14 (PD)
OUT9_PU: R1910.1, U109.15 (PU)
OUT9_SNUB: C1907.1, R1913.2
OUT9_SWITCHED: C1902.2, C1906.2, C1907.2, DCL109.2 (K), F109.1 (IN), Q109.2 (S), Q109.3 (S), Q109.4 (S), Q109.5 (S), Q109.6 (S), Q109.7 (S), Q109.8 (S), TP057.1 (OUT9_SWITCHED), U109.13 (SRC), W109.1 (POS)
OUT9_TMR: C1901.1, U109.9 (TMR)
OUT10_BST: C2002.1, U110.12 (BST)
OUT10_CS_N: C2003.2, RSH110.4 (SNS_OUT), U110.17 (CS-)
OUT10_CS_P: R2004.2, U110.18 (CS+)
OUT10_CS_P_KELVIN: R2004.1, R2006.1, RSH110.3 (SNS_IN)
OUT10_DIODE: QT110.2 (B), QT110.3 (C), U110.10 (DIODE)
OUT10_EN_UVLO: R2002.2, R2003.1, U110.1 (EN/UVLO)
OUT10_FET_DRAIN: Q110.Tab (D), R2013.1, RSH110.2 (PWR_OUT)
OUT10_GATE: C2006.1, Q110.1 (G), R2010.2, R2011.2
OUT10_IMON_RAW: R2007.1, R2008.1, U110.7 (IMON)
OUT10_ISCP: C2003.1, R2006.2, U110.19 (ISCP)
OUT10_IWRN: R2005.1, U110.8 (IWRN)
OUT10_OV: R2001.2, R2002.1, U110.2 (OV)
OUT10_PD: R2011.1, U110.14 (PD)
OUT10_PU: R2010.1, U110.15 (PU)
OUT10_SNUB: C2007.1, R2013.2
OUT10_SWITCHED: C2002.2, C2006.2, C2007.2, DCL110.2 (K), F110.1 (IN), Q110.2 (S), Q110.3 (S), Q110.4 (S), Q110.5 (S), Q110.6 (S), Q110.7 (S), Q110.8 (S), TP061.1 (OUT10_SWITCHED), U110.13 (SRC), W110.1 (POS)
OUT10_TMR: C2001.1, U110.9 (TMR)
VBAT_PROT: C1104.1, C1204.1, C1304.1, C1404.1, C1504.1, C1604.1, C1704.1, C1804.1, C1904.1, C2004.1, R1101.1, R1201.1, R1301.1, R1401.1, R1501.1, R1601.1, R1701.1, R1801.1, R1901.1, R2001.1, RSH101.1 (PWR_IN), RSH102.1 (PWR_IN), RSH103.1 (PWR_IN), RSH104.1 (PWR_IN), RSH105.1 (PWR_IN), RSH106.1 (PWR_IN), RSH107.1 (PWR_IN), RSH108.1 (PWR_IN), RSH109.1 (PWR_IN), RSH110.1 (PWR_IN), U101.20 (VS), U102.20 (VS), U103.20 (VS), U104.20 (VS), U105.20 (VS), U106.20 (VS), U107.20 (VS), U108.20 (VS), U109.20 (VS), U110.20 (VS); also elsewhere on the board

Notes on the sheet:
Work queue: CAP-OUT-INST. Ten role-free TPS48110-Q1 channels implement the accepted 80 V TOLL architecture. Each channel includes a four-terminal shunt, 55.7 V/6.0 V OV/UVLO ladder, hardware current thresholds, timer, bootstrap, replaceable PU/PD resistors, DNP slew/snubber sites, independent remot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

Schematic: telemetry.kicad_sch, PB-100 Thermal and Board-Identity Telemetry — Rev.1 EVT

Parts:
C61, C64, C67: 10nF 50V X7R; C0603
R61, R64, R67: 4.7k 1% AEC-Q200; R0603
R62, R65, R68: 1k 1% ADC SERIES; R0603
RID1: PB REV1 ID: 10k/10k 0.1% DIVIDER; Board_ID_Divider_0603x2
RT1, RT2, RT3: NTCGS103JF103FT8 10k 1% B3435 AEC-Q200; R0402
TP002: TEST AGND; TestPoint_SMD_1.5mm
TP012: TEST LB_3V3_IO; TestPoint_SMD_1.5mm
TP013: TEST PB_I2C_SCL; TestPoint_SMD_1.5mm
TP014: TEST PB_I2C_SDA; TestPoint_SMD_1.5mm
TP015: TEST PB_I2C_INT; TestPoint_SMD_1.5mm
TP016: TEST TEMP_PCB; TestPoint_SMD_1.5mm
TP017: TEST TEMP_PWR_A; TestPoint_SMD_1.5mm
TP018: TEST TEMP_PWR_B; TestPoint_SMD_1.5mm
TP019: TEST CAN1_TX_DISABLE_CMD; TestPoint_SMD_1.5mm
TP020: TEST CAN1_TX_DISABLED_STATUS; TestPoint_SMD_1.5mm
TP021: TEST CAN1_RX_ROUTE; TestPoint_SMD_1.5mm

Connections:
LB_3V3_IO: R61.1, R64.1, R67.1, RID1.1 (LB_3V3_IO), TP012.1 (LB_3V3_IO); also elsewhere on the board
TEMP_PCB_RAW: R61.2, R62.1, RT1.1
TEMP_PWR_A_RAW: R64.2, R65.1, RT2.1
TEMP_PWR_B_RAW: R67.2, R68.1, RT3.1

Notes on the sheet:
Work queue: CAP-TEL. Three role-independent 10k AEC-Q200 NTC dividers use 4.7k pull-ups to LB_3V3_IO, 1k ADC isolation, and 10nF filters. Sensor placement targets board reference, input/OUT2 hot zone, and medium-output/buck zone. RID1 is a physical two-resistor board-ID divider. Calibration and thr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

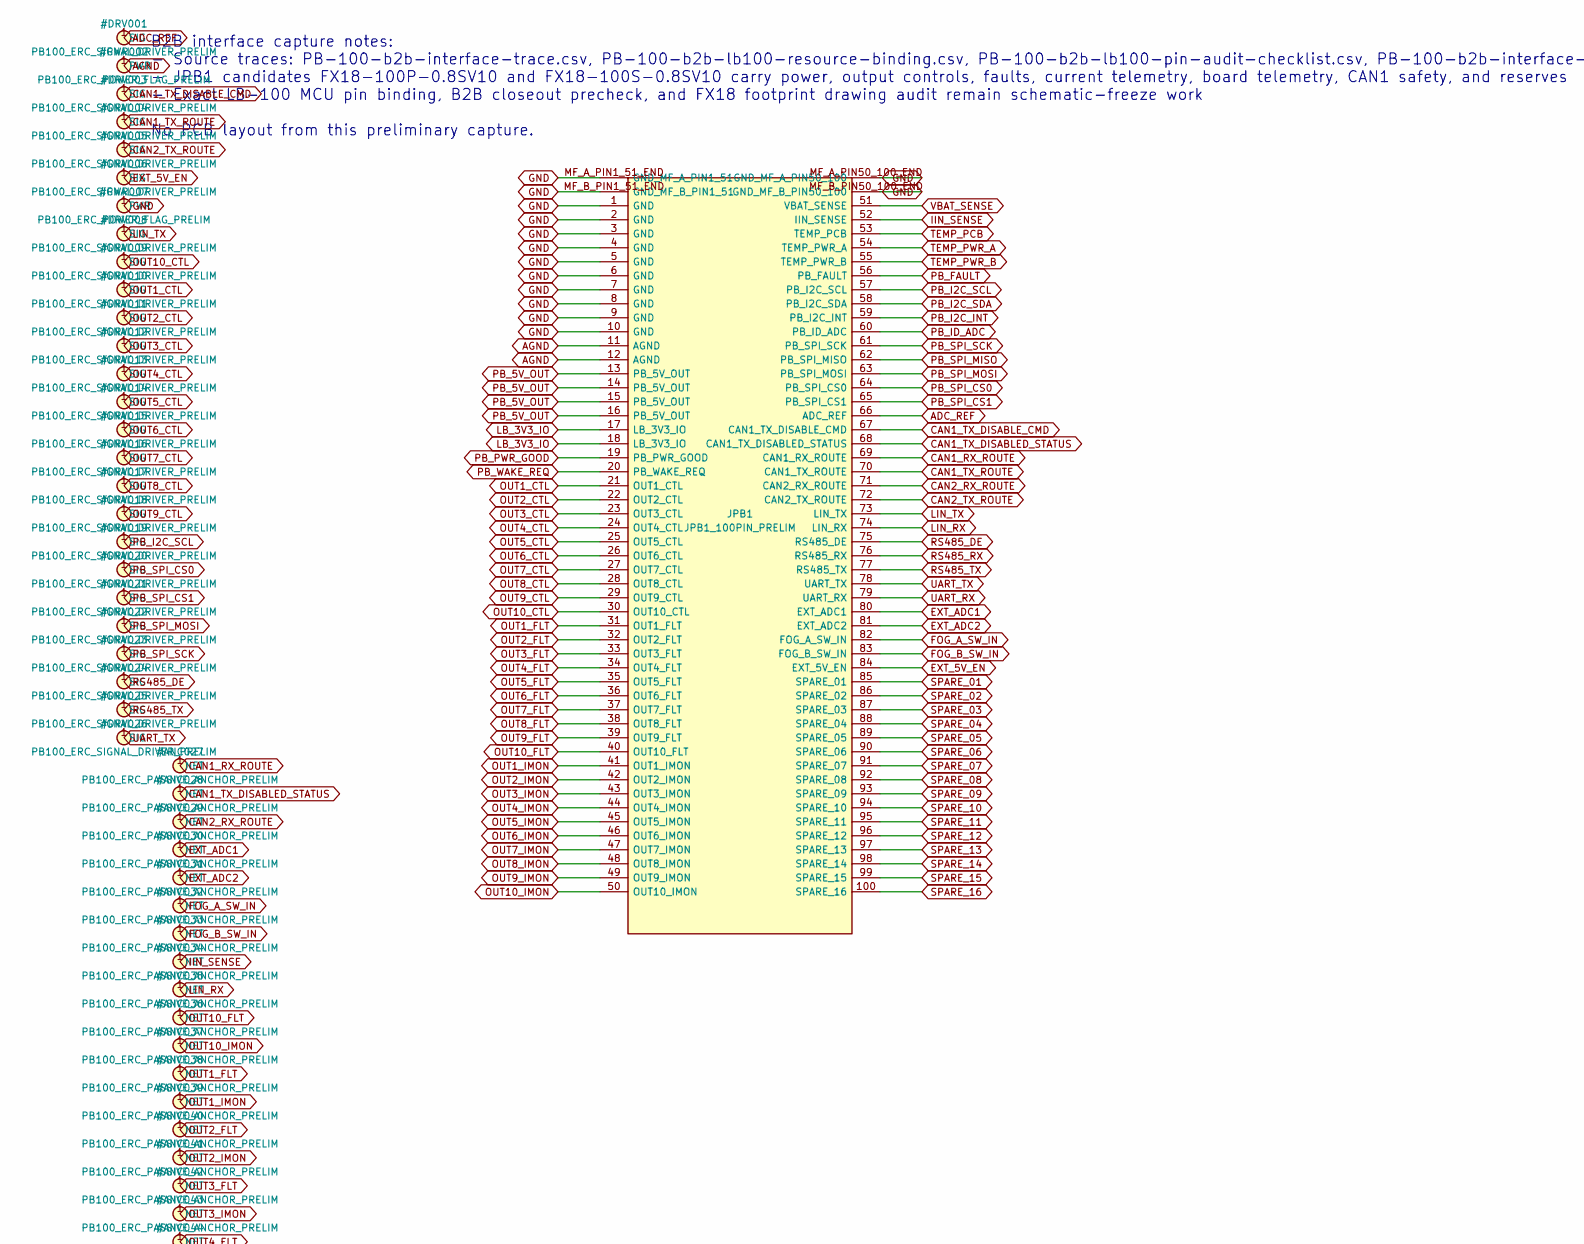
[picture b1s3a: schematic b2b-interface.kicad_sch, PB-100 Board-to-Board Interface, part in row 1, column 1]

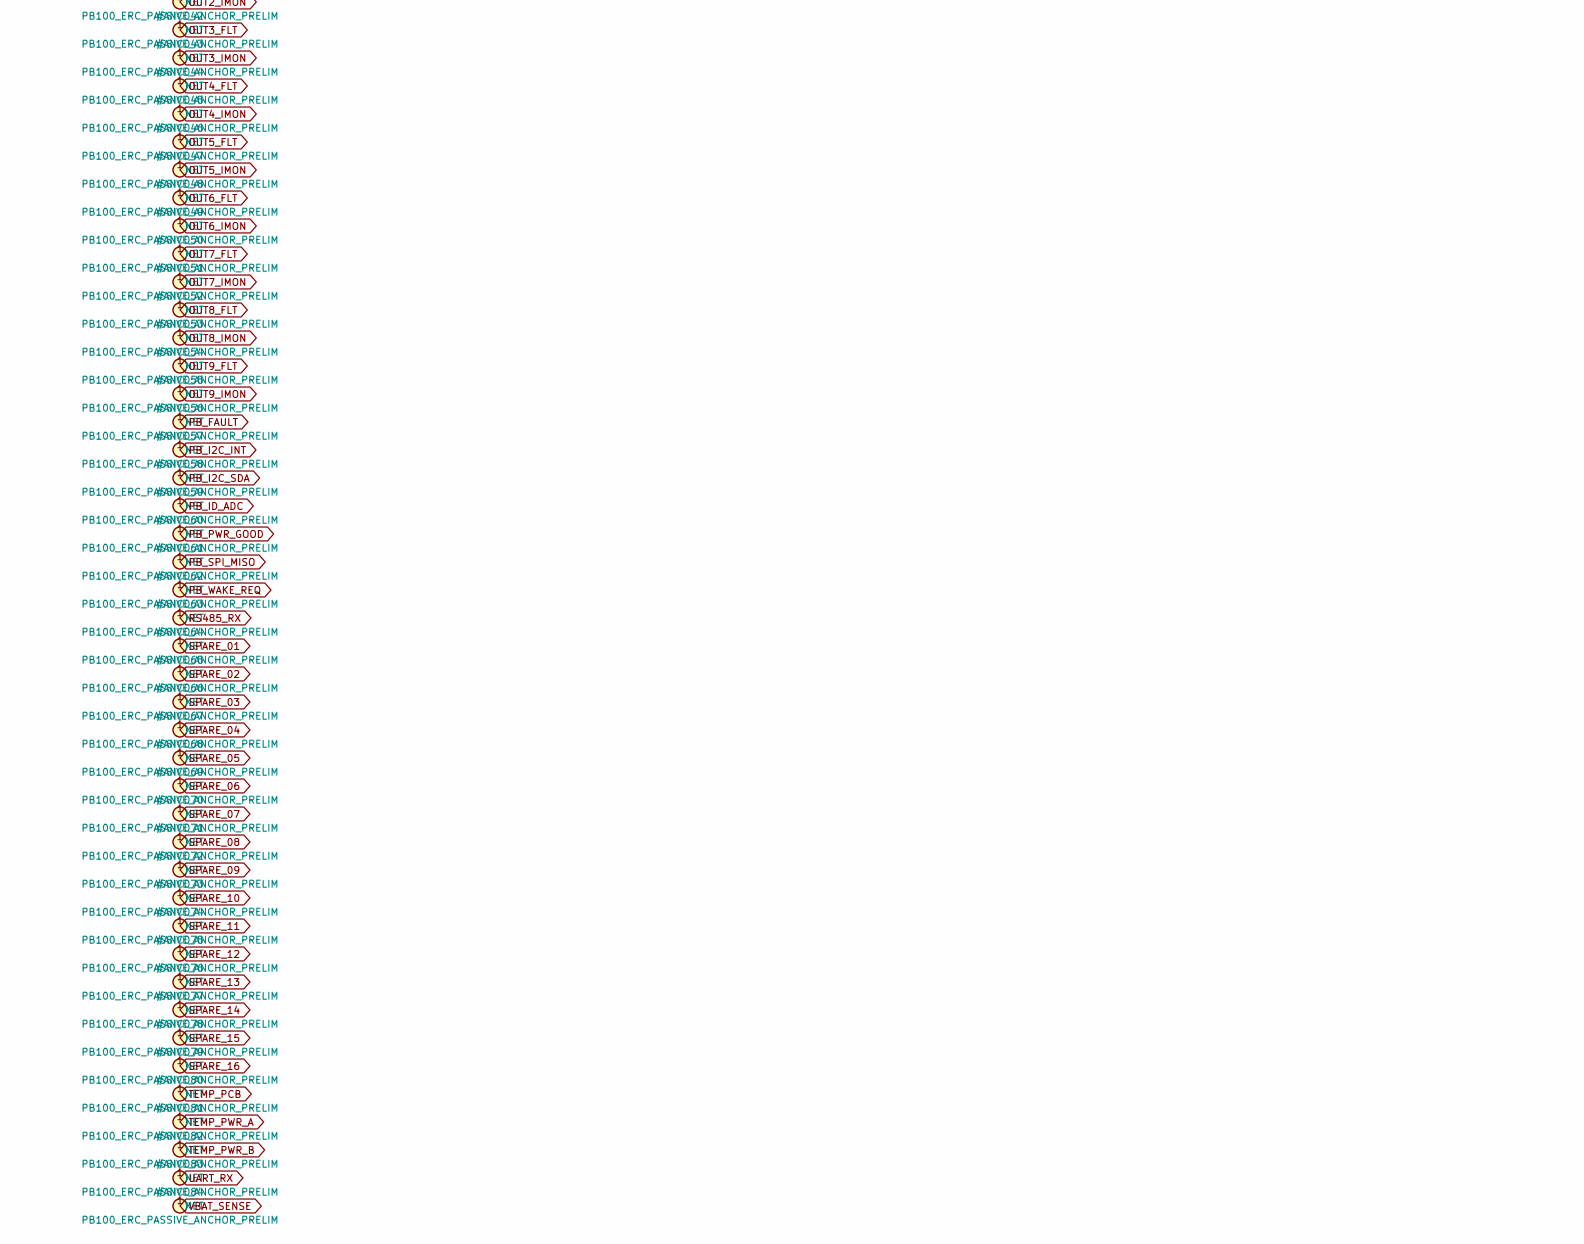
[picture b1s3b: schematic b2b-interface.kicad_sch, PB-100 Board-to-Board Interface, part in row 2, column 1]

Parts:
JPB1: JPB1_100PIN_PRELIM; FX18-100P-0.8SV10_Hirose

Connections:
LB_3V3_IO: JPB1.17 (LB_3V3_IO), JPB1.18 (LB_3V3_IO); also elsewhere on the board
PB_5V_OUT: JPB1.13 (PB_5V_OUT), JPB1.14 (PB_5V_OUT), JPB1.15 (PB_5V_OUT), JPB1.16 (PB_5V_OUT); also elsewhere on the board

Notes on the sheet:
B2B interface capture notes: - Source traces: PB-100-b2b-interface-trace.csv, PB-100-b2b-lb100-resource-binding.csv, PB-100-b2b-lb100-pin-audit-checklist.csv, PB-100-b2b-interface-freeze-checklist.csv, PB-100-b2b-interface-closeout-precheck.csv, PB-100-b2b-pin-map.csv, PB-100-b2b-pin-budget.csv - J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
